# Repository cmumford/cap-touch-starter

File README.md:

# Introduction

This is a simple hardware/software starter project containing an
MCU (ESP32), and a capacitive touch screen. Nothing fancy, just
something to fork when starting a new project that needs these capabilities.

# Main Components

* ESP32-WROVER-E ([Datasheet](https://www.espressif.com/sites/default/files/documentation/esp32-wrover_datasheet_en.pdf))
* [2.8" TFT Display - 240x320 with Capacitive Touchscreen](https://www.adafruit.com/product/2770)
* CP2102N ([Datasheet](https://www.silabs.com/documents/public/data-sheets/cp2102n-datasheet.pdf))
* SPIRAM.
* 10-pin JTAG debug port.

# Board Design

See the [pcb/](pcb/) folder for the schematic and board layout.

# Software

It includes a starter application built with the
[ESP-IDF](https://github.com/espressif/esp-idf) platform framework. The application
[lv_demos](https://github.com/lvgl/lv_demos) which is part of the [LVGL](https://lvgl.io/)
graphics library. This could easily be replaced with a different application

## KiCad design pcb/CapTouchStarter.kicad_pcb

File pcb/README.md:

# Schematic

[Schematic](Schematic.pdf)

# Layout

[Layout](Layout.pdf)

# BOM

| Quantity | Description                      | Value           | Package            |
| -------- | -------------------------------- | --------------- | ------------------ |
| 3        | Capacitor                        | 22μF/6.3V       | 0603 (1608 Metric) |
| 5        | Capacitor                        | 0.1μF/50V       | 0603 (1608 Metric) |
| 1        | Capacitor                        | 4.7μF/6.3V      | 0603 (1608 Metric) |
| 1        | Diode (Schottsky)                | BAT760-7        | SOD-323            |
| 1        | Voltage suppressor               | SP0503BAHT      | SOT-143            |
| 4        | LED                              | LED             | 0603 (1608 Metric) |
| 1        | USB Type-C Receptacle            | [12401548E412A](https://www.digikey.com/en/products/detail/amphenol-icc-commercial-products/12401548E412A/13683580)   |                    |
| 1        | 2.8" LCD w/Capacitive Touch      | [DT280QV10-CT](https://www.adafruit.com/product/2770) |  |
| 1        | Flat pack ribbon cable connector | 62684-502100ALF | 50 pin 0.5 mm pitch |
| 2        | NPN Transistor                   | SS8050-G        | SOT-23             |
| 4        | Resistor                         | 68Ω             | 0603 (1608 Metric) |
| 3        | Resistor                         | 2KΩ             | 0603 (1608 Metric) |
| 1        | Resistor                         | 22K1Ω           | 0603 (1608 Metric) |
| 1        | Resistor                         | 47K5Ω           | 0603 (1608 Metric) |
| 4        | Resistor                         | 10KΩ            | 0603 (1608 Metric) |
| 2        | Resistor                         | 5K1Ω            | 0603 (1608 Metric) |
| 2        | Resistor                         | 2K2Ω            | 0603 (1608 Metric) |
| 1        | ESP32-WROVER-E                   |                 |                    |
| 1        | SPIRAM (8 MB)                    | LY68L6400SLIT   | SOP-8              |
| 1        | Voltage Regulator                | AMS1117-3.3     | SOT-223            |
| 1        | Voltage Detector                 | [BD48K33G-TLCT-ND](https://fscdn.rohm.com/en/products/databook/datasheet/ic/power/voltage_detector/bd48xxg-e.pdf) | SOT-23-3           |
| 1        | USB-to-UART bridge controller    | CP2102N-A01     | QFN-28             |
| 2        | Tactile pushbutton               |                 |                    |
| 1        | Slider 1P2T switch               | SK-12D07        |                    |

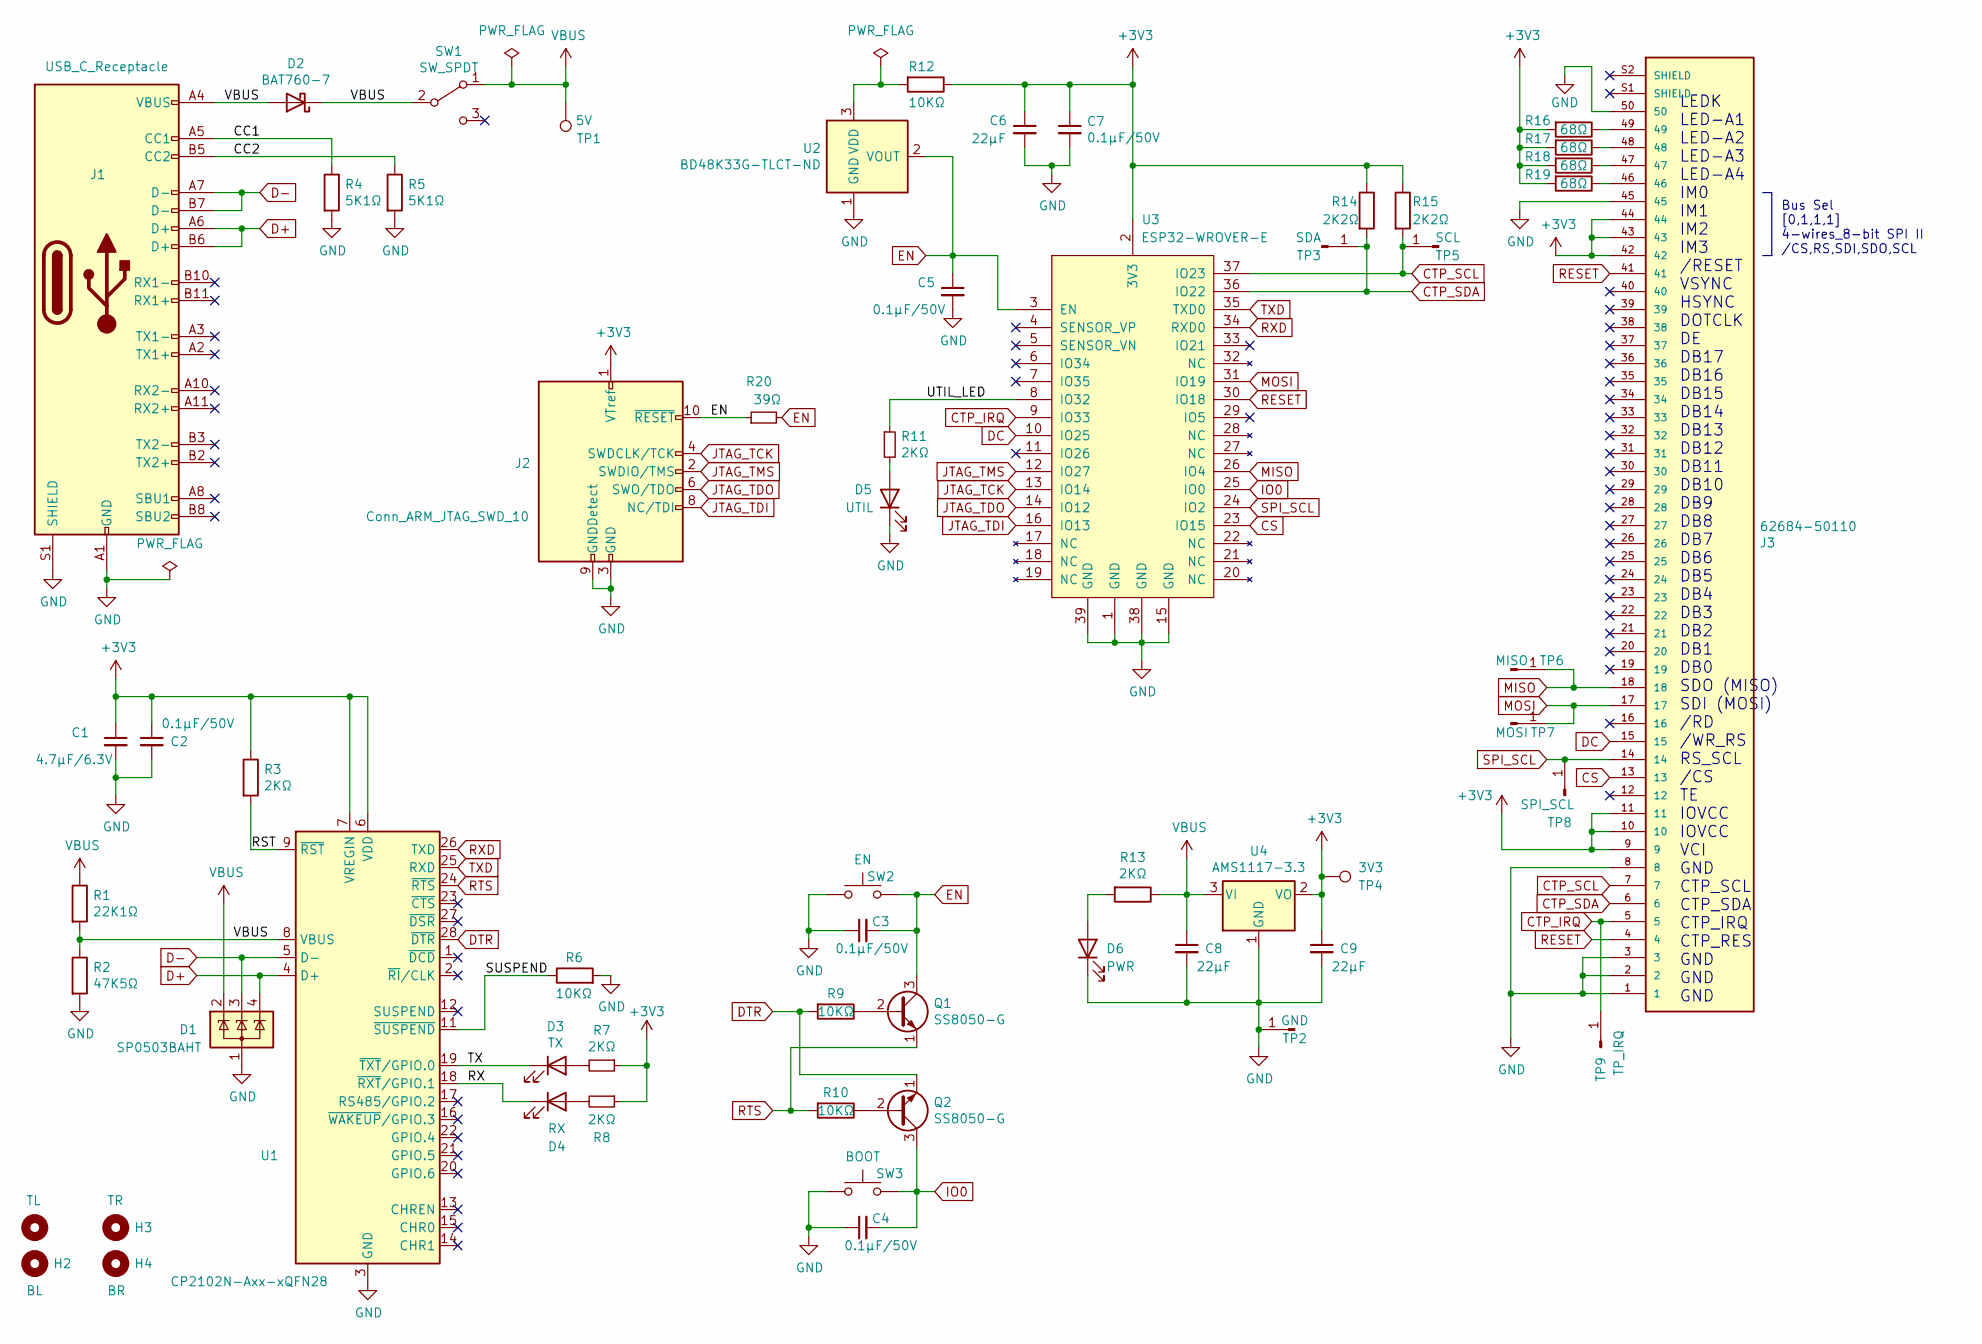
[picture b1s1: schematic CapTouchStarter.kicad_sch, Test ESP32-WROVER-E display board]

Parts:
C1: 4.7μF/6.3V; C_0603_1608Metric
C2, C3, C4, C5, C7: 0.1μF/50V; C_0603_1608Metric
C6, C8, C9: 22μF; C_0603_1608Metric
D1: SP0503BAHT; SOT-143
D2: BAT760-7; D_SOD-323
D3: TX; LED_0603_1608Metric
D4: RX; LED_0603_1608Metric
D5: UTIL; LED_0603_1608Metric
D6: PWR; LED_0603_1608Metric
H1: TL; MountingHole_2.2mm_M2
H2: BL; MountingHole_2.2mm_M2
H3: TR; MountingHole_2.2mm_M2
H4: BR; MountingHole_2.2mm_M2
J1: USB_C_Receptacle; USB_C_Receptacle_Amphenol_12401548E4-2A
J2: Conn_ARM_JTAG_SWD_10; PinHeader_2x05_P1.27mm_Vertical
J3: 62684-50110
Q1, Q2: SS8050-G; SOT-23
R1: 22K1Ω; R_0603_1608Metric
R2: 47K5Ω; R_0603_1608Metric
R3, R7, R8, R11, R13: 2KΩ; R_0603_1608Metric
R4, R5: 5K1Ω; R_0603_1608Metric
R6, R9, R10, R12: 10KΩ; R_0603_1608Metric
R14, R15: 2K2Ω; R_0603_1608Metric
R16, R17, R18, R19: 68Ω; R_0603_1608Metric
R20: 39Ω; R_0603_1608Metric
SW1: SW_SPDT; SW_Slide_1P2T_CK_OS102011MS2Q
SW2: EN; SW_PUSH_6mm_H5mm
SW3: BOOT; SW_PUSH_6mm_H5mm
TP1: 5V; TestPoint_Pad_D2.5mm
TP2: GND; TestPoint_Loop_D2.50mm_Drill1.0mm
TP3: SDA; TestPoint_Loop_D2.50mm_Drill1.0mm
TP4: 3V3; TestPoint_Pad_D2.5mm
TP5: SCL; TestPoint_Loop_D2.50mm_Drill1.0mm
TP6: MISO; TestPoint_Loop_D2.50mm_Drill1.0mm
TP7: MOSI; TestPoint_Loop_D2.50mm_Drill1.0mm
TP8: SPI_SCL; TestPoint_Loop_D2.50mm_Drill1.0mm
TP9: TP_IRQ; TestPoint_Loop_D2.50mm_Drill1.0mm
U1: CP2102N-Axx-xQFN28; QFN-28-1EP_5x5mm_P0.5mm_EP3.35x3.35mm
U2: BD48K33G-TLCT-ND; SOT-23
U3: ESP32-WROVER-E; ESP32-WROVER-IE
U4: AMS1117-3.3; SOT-223-3_TabPin2

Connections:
+3V3: C1.1, C2.1, C6.1, C7.1, C9.1, J2.1 (VTref), J3.9, J3.10, J3.11, J3.42, J3.43, J3.44, R3.1, R7.1, R8.1, R12.1, R14.1, R15.1, R16.2, R17.2, R18.2, R19.2, TP4.1, U1.6 (VDD), U1.7 (VREGIN), U3.2 (3V3), U4.2 (VO)
/CC1: J1.A5 (CC1), R4.1
/CC2: J1.B5 (CC2), R5.1
/RST: R3.2, U1.9 (~RST)
/RX: D4.1 (K), U1.18 (~RXT/GPIO.1)
/SUSPEND: R6.1, U1.11 (~SUSPEND)
/TX: D3.1 (K), U1.19 (~TXT/GPIO.0)
/UTIL_LED: R11.1, U3.8 (IO32)
CS: J3.13, U3.23 (IO15)
CTP_IRQ: J3.5, TP9.1, U3.9 (IO33)
CTP_SCL: J3.7, R15.2, TP5.1, U3.37 (IO23)
CTP_SDA: J3.6, R14.2, TP3.1, U3.36 (IO22)
D+: D1.4 (K), J1.A6 (D+), J1.B6 (D+), U1.4 (D+)
D-: D1.3 (K), J1.A7 (D-), J1.B7 (D-), U1.5 (D-)
DC: J3.15, U3.10 (IO25)
DTR: Q2.1 (E), R9.2, U1.28 (~DTR)
EN: C3.2, C5.1, J2.10 (~RESET), Q1.3 (C), R20.1, R20.2, SW2.2, U2.2 (VOUT), U3.3 (EN)
GND: C1.2, C2.2, C3.1, C4.1, C5.2, C6.2, C7.2, C8.2, C9.2, D1.1 (A), D5.1 (K), D6.1 (K), J1.A1 (GND), J1.A12 (GND), J1.B1 (GND), J1.B12 (GND), J1.S1 (SHIELD), J2.3 (GND), J2.5 (GND), J2.9 (GNDDetect), J3.1, J3.2, J3.3, J3.8, J3.45, J3.50, R2.2, R4.2, R5.2, R6.2, SW2.1, SW3.1, TP2.1, U1.3 (GND), U1.29 (GND), U2.1 (GND), U3.1 (GND), U3.15 (GND), U3.38 (GND), U3.39 (GND), U4.1 (GND)
IO0: C4.2, Q2.3 (C), SW3.2, U3.25 (IO0)
JTAG_TCK: J2.4 (SWDCLK/TCK), U3.13 (IO14)
JTAG_TDI: J2.8 (NC/TDI), U3.16 (IO13)
JTAG_TDO: J2.6 (SWO/TDO), U3.14 (IO12)
JTAG_TMS: J2.2 (SWDIO/TMS), U3.12 (IO27)
MISO: J3.18, TP6.1, U3.26 (IO4)
MOSI: J3.17, TP7.1, U3.31 (IO19)
unnamed: D3.2 (A), R7.2
unnamed: D4.2 (A), R8.2
unnamed: D5.2 (A), R11.2
unnamed: D6.2 (A), R13.2
unnamed: J3.46, R19.1
unnamed: J3.47, R18.1
unnamed: J3.48, R17.1
unnamed: J3.49, R16.1
unnamed: Q1.2 (B), R9.1
unnamed: Q2.2 (B), R10.1
unnamed: R12.2, U2.3 (VDD)
RESET: J3.4, J3.41, U3.30 (IO18)
RTS: Q1.1 (E), R10.2, U1.24 (~RTS)
RXD: U1.26 (TXD), U3.34 (RXD0)
SPI_SCL: J3.14, TP8.1, U3.24 (IO2)
TXD: U1.25 (RXD), U3.35 (TXD0)
VBUS: C8.1, D1.2 (K), D2.1 (K), D2.2 (A), J1.A4 (VBUS), J1.A9 (VBUS), J1.B4 (VBUS), J1.B9 (VBUS), R1.1, R1.2, R2.1, R13.1, SW1.1 (A), SW1.2 (B), TP1.1, U1.8 (VBUS), U4.3 (VI)

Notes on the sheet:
LEDK LED-A1 LED-A2 LED-A3 LED-A4 IM0 IM1 IM2 IM3 /RESET VSYNC HSYNC DOTCLK DE DB17 DB16 DB15 DB14 DB13 DB12 DB11 DB10 DB9 DB8 DB7 DB6 DB5 DB4 DB3 DB2 DB1 DB0 SDO (MISO) SDI (MOSI) /RD /WR_RS RS_SCL /CS TE IOVCC IOVCC VCI GND CTP_SCL CTP_SDA CTP_IRQ CTP_RES GND GND GND
Bus Sel [0,1,1,1] 4-wires_8-bit SPI II /CS,RS,SDI,SDO,SCL

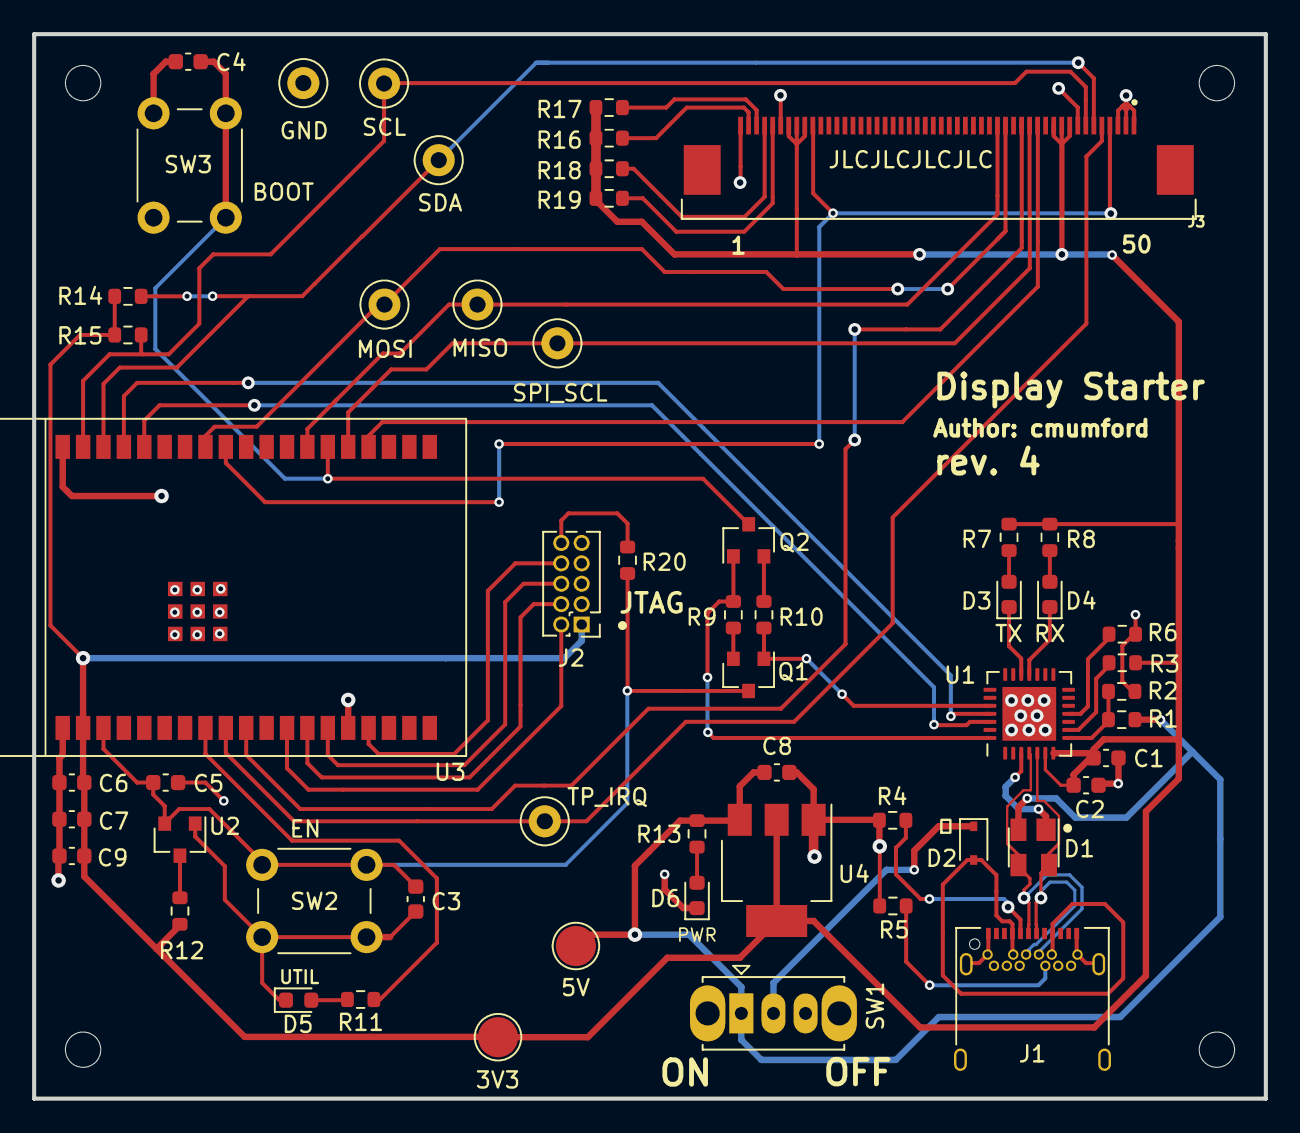
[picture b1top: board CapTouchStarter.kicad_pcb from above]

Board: 4 copper layers, 76.7 x 66.3 mm, 60 parts (0 on the bottom side), 42 nets.

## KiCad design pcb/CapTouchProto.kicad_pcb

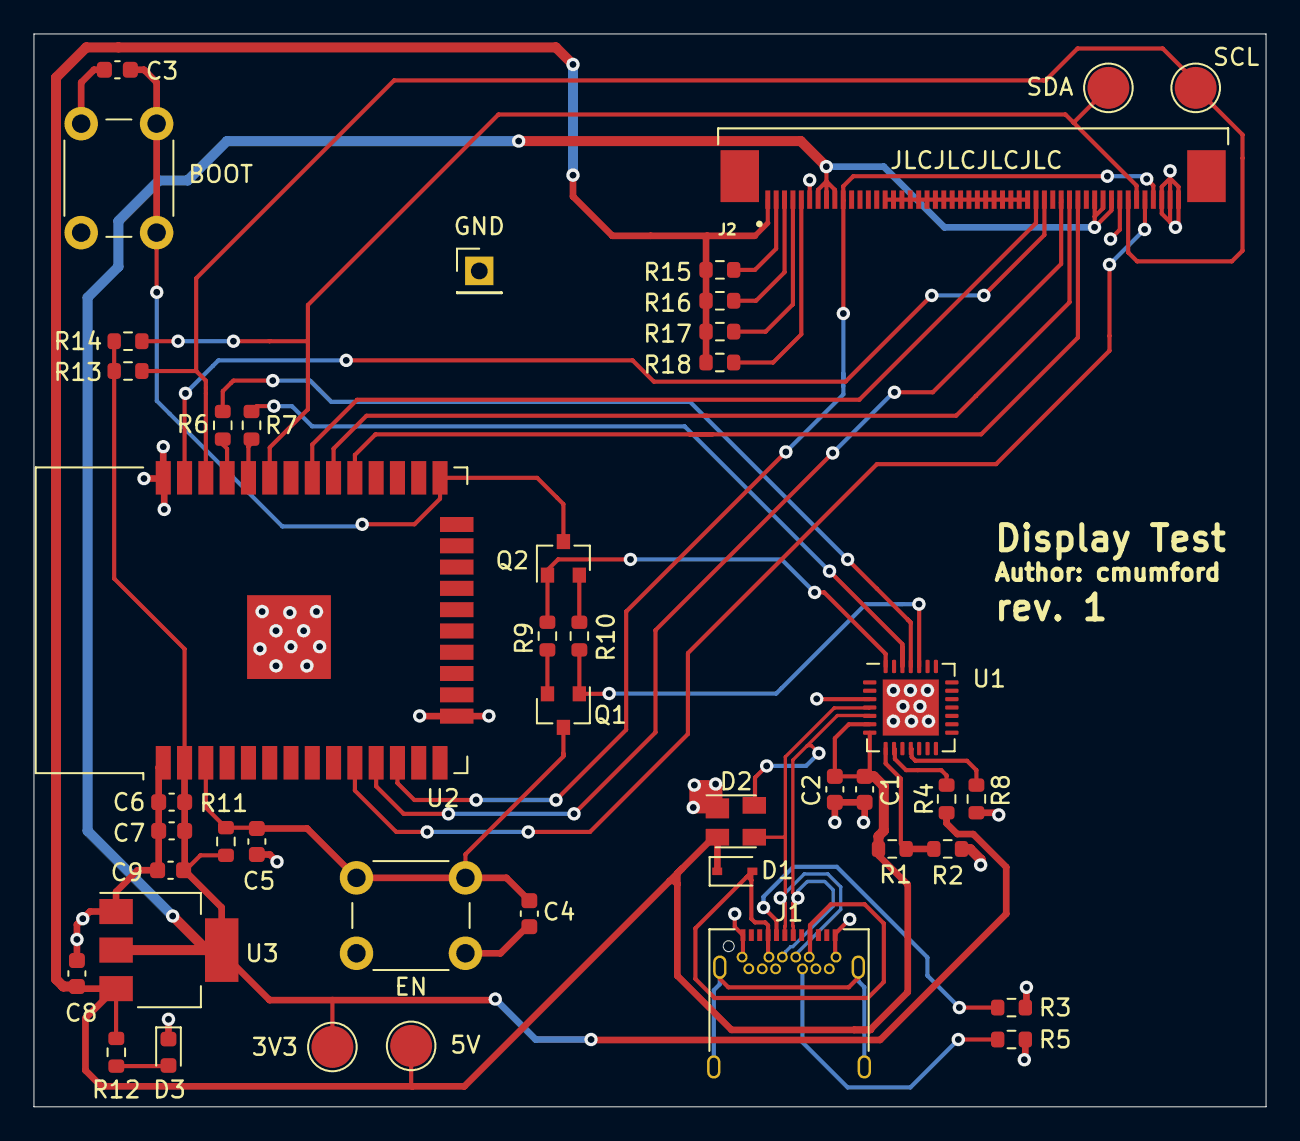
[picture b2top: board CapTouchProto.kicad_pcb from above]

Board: 2 copper layers, 73.5 x 64.0 mm, 44 parts (0 on the bottom side), 36 nets.

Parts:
3V3: 3V3; TestPoint_Pad_D2.5mm
5V: 5V; TestPoint_Pad_D2.5mm
BOOT: SW_Push; SW_PUSH_6mm_H5mm
C1: 4.7μF/6.3V; C_0603_1608Metric
C2: 0.1μF/50V; C_0603_1608Metric
C3, C4, C5, C7: 0.1μF; C_0603_1608Metric
C6, C8, C9: 22μF; C_0603_1608Metric
D1: BAT760-7; D_SOD-323
D2: SP0503BAHT; SOT-143
D3: LED (red); LED_0603_1608Metric
EN: SW_Push; SW_PUSH_6mm_H5mm
GND: Conn_01x01_Male; PinHeader_1x01_P2.54mm_Vertical
J1: USB_C_Receptacle; USB_C_Receptacle_Amphenol_12401548E4-2A
J2: 62684-50110
Q1, Q2: SS8050-G; SOT-23
R1: 22.1KΩ; R_0603_1608Metric
R2: 47.5KΩ; R_0603_1608Metric
R3, R5: 5K1Ω; R_0603_1608Metric
R4: 2KΩ; R_0603_1608Metric
R6, R7: 0Ω; R_0603_1608Metric
R8, R11: 10KΩ; R_0603_1608Metric
R9, R10: 10K; R_0603_1608Metric
R12: 2K (5%); R_0603_1608Metric
R13, R14: 2K2Ω; R_0603_1608Metric
R15, R16, R17, R18: 68Ω; R_0603_1608Metric
SCL: SCL; TestPoint_Pad_D2.5mm
SDA: SDA; TestPoint_Pad_D2.5mm
U1: CP2102N-A01-GQFN28; QFN-28-1EP_5x5mm_P0.5mm_EP3.35x3.35mm
U2: 1965-ESP32-WROOM-32E(8MB)CT-ND; ESP32-WROOM-32
U3: AMS1117-3.3; SOT-223-3_TabPin2

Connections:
+3V3: 3V3.1, C6.1, C7.1, C9.1, J2.7, J2.8, J2.9, J2.40, J2.41, J2.42, R4.1, R11.1, R13.1, R14.1, U2.2, U3.2
D+: D2.3, J1.A6, J1.B6, U1.4
D-: D2.4, J1.A7, J1.B7, U1.5
DTR: Q2.1, R9.2, U1.28
EN: C4.2, C5.1, EN.2, Q1.3, R11.2, U2.3
GND: BOOT.1, C1.2, C2.2, C3.1, C4.1, C5.2, C6.2, C7.2, C8.2, C9.2, D2.1, D3.1, EN.1, GND.1, J1.A1, J1.A12, J1.B1, J1.B12, J2.6, J2.43, J2.48, J2.49, J2.50, R2.2, R3.2, R5.2, R8.2, U1.3, U1.29, U2.1, U2.15, U2.38, U2.39, U3.1
IO0: BOOT.2, C3.2, Q2.3, U2.25
unnamed: D1.2, J1.A4, J1.A9, J1.B4, J1.B9
unnamed: D3.2, R12.2
unnamed: J1.A5, R3.1
unnamed: J1.B5, R5.1
unnamed: J2.2, R15.1
unnamed: J2.3, R16.1
unnamed: J2.4, R17.1
unnamed: J2.5, R18.1
unnamed: J2.10, J2.47, U2.12
unnamed: J2.15, J2.16, J2.17, J2.18, J2.19, J2.20, J2.21, J2.22, J2.23, J2.24, J2.25, J2.26, J2.27, J2.28, J2.29, J2.30, J2.31, J2.32
unnamed: J2.33, U2.31
unnamed: J2.34, U2.37
unnamed: J2.36, U2.11
unnamed: J2.37, U2.30
unnamed: J2.38, U2.29
unnamed: J2.44, R13.2, SCL.1, U2.36
unnamed: J2.45, R14.2, SDA.1, U2.33
unnamed: J2.46, U2.10
unnamed: Q1.2, R9.1
unnamed: Q2.2, R10.1
unnamed: R1.2, R2.1, U1.8
unnamed: R4.2, U1.9
unnamed: R6.2, U1.25
unnamed: R7.2, U1.26
unnamed: R8.1, U1.11
RTS: Q1.1, R10.2, U1.24
RXD: R7.1, U2.34
TXD: R6.1, U2.35
VBUS: 5V.1, C1.1, C2.1, C8.1, D1.1, D2.2, J2.1, R1.1, R12.1, R15.2, R16.2, R17.2, R18.2, U1.6, U1.7, U3.3

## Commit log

2021-09-04 Added .gitattributes.
2021-09-04 Added .gitignore.
2021-09-04 Add footprint+symbol for 62684-50110.
    This is a 50-pin 0.5mm pitch flat panel connector (FPC).
    https://www.adafruit.com/product/1492
2021-09-04 Added flat panel connector to schematic.
2021-09-05 Some schematic wire-up.
2021-09-05 Add ESP32-WROOM-32E symbol+footprint.
2021-09-05 Lots of connecting up stuff.
2021-09-05 A little layout.
2021-09-06 more layout.
2021-09-06 Layout of usb-c power.
2021-09-06 Getting closer.
2021-09-06 Transistors to SOT-23.
2021-09-06 power routed.
2021-09-06 USB-C 5.1K resistor layout.
2021-09-06 Layout done.
2021-09-06 Specified 6mmx5mm tactile buttons.
2021-09-06 Add test points.
2021-09-07 Settings for creating Gerber files.
2021-09-07 Add schematic + board layout PDFs.
2021-09-25 Added dot for CP2102N pin 1.
2021-09-26 Moved some passives on layout for better labeling.
2021-09-26 Testpoint changes.
2021-09-26 Fix switch labeling, more cleanup.
2021-09-26 CP2102 VCC/REGIN pins to 3.3V instead of VBUS.
    Oops!
2021-10-02 STL for 5-1734592-0
    From https://www.te.com/usa-en/product-5-1734592-0.html
2021-10-03 Added README.
2021-10-03 Unified value names.
    Renamed component values so that the coalesce into groups
    when creating a BOM.
2021-10-03 Added submodules: lvgl, lvgl_esp32_drivers.
2021-10-08 Added project build files.
2021-10-08 Set pins for this board.
    Working for ESP32-WROOM-32D.
    I believe this has no integrated SPIRAM.
2021-10-08 Added README docs.
2021-10-08 Add lv_examples.
    Add the lv_examples submodule and use the widget slideshow
    as the application main body.
2021-10-08 Printing out memory info at startup.
    ```
    I (317) App: CapTouchProto app!
    I (317) App: This is esp32 chip with 2 CPU core(s), WiFi/BT/BLE.
    I (327) App: Silicon revision 3.
    I (327) App: 4 MB external flash
    I (337) App: Free heap size: 292772 bytes.
2021-10-08 Upgraded LVGL to v8.
2021-10-08 Increased external SPI flash size to 4MB.
2021-10-08 Git-ignoring build/ & sdkconfig.
2021-10-08 Added application boilerplate.
2021-10-08 sdkconfig: Defining LVGL fonts.
2021-10-10 Switched display mode to 4-wires_8-bit SPI.
    Set the interface mode pins (IM0..IM3) to [0, 1, 1, 0].
2021-10-10 Connected display backlight cathode (LEDK) to GND.
2021-10-10 WIP: Changes to LVGL Display config.
2021-10-10 Renamed KiCad project files to match repo name.
2021-10-10 Using 3V3 for display VCC.
2021-10-10 sdkconfig: Added section comments.
    Makes comparing configured defaults easier.
2021-10-10 Added script to delete files.
    Simplify the cleaning process with a script to delete files/dirs.
    Adding this because PowerShell's Remove-Item command doesn't take
    multiple args, and also returns a non-zero error code for nonexistent
    items - even with the `-ErrorAction Ignore` argument.
2021-10-10 LVGL display: VSPI, MISO.
2021-10-10 Disabled custom LVGL SPI frequency.
2021-10-10 LVGL: half => full duplex.
2021-10-10 display sdkconfig.default values.
2021-10-11 sdkconfig: Added FT6X06 touch controller to LVGL config.
    Board uses FT6206 touch controller. Using I2C bus 0 with standard
    configuration.
2021-10-11 Back to 4-wire SPI II bus.
    Bus Sel
    [0,1,1,1]
    4-wires_8-bit SPI II
    /CS,RS,SDI,SDO,SCL
2021-10-11 Corrected LCD pin order.
    The 50-pin flat pack ribbon cable has reversed pin ordering.
2021-10-11 Removed 0Ω TX/RX resistors.
    Also minor routing cleanup.
2021-10-11 Added TX/RX LED's.
    Also, layout cleanup.
2021-10-11 Update layout/schematic PDFs.
    And update board design version to 2.
2021-10-11 Added display silkscreen pin numbers.
2021-10-11 Add SPI test points.
2021-10-12 Use global labels to cleanup schematic.
2021-10-12 Move GND test pad below voltage regulator in schematic.
    No changes to layout.
2021-10-12 Combine DTR/RTS EN/IO0 sections.
2021-10-12 Add JTAG debugger connector.
2021-10-12 Add pin 1 identifiers.
    Also move 3V3 and 5V test pads (make inline).
2021-10-12 Import JLCPCB design rules for 1-2 layer boards.
    Source: https://github.com/sethhillbrand/kicad_templates
2021-10-12 Updated PDFs.
2021-11-13 Using FPC STP file.
2021-11-13 Add a voltage detector.
    Add a BD48K33G-TLCT-ND voltage detector.
2021-11-13 Added power switch.
    A horizontal slider switch to enable/disable entire device.
2021-11-13 More route cleanup.
2021-11-13 Documented starter source.
2021-11-13 Disabled built-in ESP32 I2C pullup resistors.
2021-11-13 pcb: Very minor alignments and clenup.
2021-11-13 pcb: Added r3. TODO items.
2021-11-13 Added library for LY68L6400SLIT.
    https://datasheet.lcsc.com/lcsc/1809140531_Lyontek-Inc--LY68L6400SLIT_C261881.pdf
2021-11-13 Moved TP_IRQ label.
2021-11-13 Disabled mbedTLS trusted root certificate bundle.
    Certificate bundle has expired/invalid certs, so disabled as per:
    See https://github.com/espressif/esp-idf/issues/7621
    This should be temporary once ESP-IDF is updated.
2021-11-13 Resetting touch panel.
2021-11-13 Layout with PSRAM.
2021-11-13 Added 50-pin FPC connector symbol.
    Molex.
    Mfr. part: 0541325062
2021-11-13 Updated schematic PDF.
2021-11-13 Using pdMS_TO_TICKS macro.
2021-11-13 Cleanup.
2021-11-13 Added mounting holes for standoffs.
    Not pretty, but should work.
2021-11-13 Added PSRAM to circuit.
    https://pcbartists.com/design/embedded/esp32-psram-schematic-notes/
2021-11-13 Rename lv_examples to lv_demos.
    lv_examples seems to have been renamed upstream to lv_demos. Navigating
    to https://github.com/lvgl/lv_examples.git redirects to
    https://github.com/lvgl/lv_demos. This projects lv_examples directory
    started out as a copy of
    https://github.com/lvgl/lv_port_esp32/tree/master/components/lv_examples
    which appears to be before the rename.
2021-11-13 Moved voltage regulator in layout.
2021-11-13 Ordered pcb todo by priority.
2021-11-13 Added antenna keep-out zone for copper fill.
2021-11-13 Fixed ground via overlapping display anchor pad.
2021-11-13 Removed 0Ω resistors from the BOM.
    These were in rev 1 for testing, but no longer used.
2021-11-13 Fix LCD product link.
2021-11-13 Improve software description in README.
2021-11-13 Move pushbutton near switch in README
    Like with like.
2021-11-13 Added serial port enumerators.
2021-11-13 Add openocd target.
2021-11-14 Added utility LED connected to IO32.
2021-11-14 Added voltage detector datasheet link.
2021-11-14 Got LED's working.
    No change required. Needed to use Simplicity Studio's Xpress
    Configurator to set GPIO0/1's alternate configuration to
    TX/RX Toggle respectively.
2021-11-14 Figured out capacitive touch issue.
    Corrent board has a solder bridge that shorts SCL to GND. Hopefully
    that is the only problem.
2021-11-14 Keepig current ESD solution.
    May change in a future rev.
2021-11-14 Refilled ground pour.
2021-11-14 Updated layout/schematic PDFs.
2021-11-14 Add missing trace for UTIL LED.
2021-11-14 New layout PDF.
2021-11-14 Added board render image.
2021-11-14 Added SPIRAM to README.
2021-11-15 README text tweak.
2021-11-26 Changed schematic version to 3.
2021-11-26 Cleaning KiCAD intermediate files.
2021-11-26 Add more space between GND and 3v3 on display connector.
2021-11-26 Switched JTAG footprint to 3220-10-0100-00.
2021-11-26 Turning on UTIL LED at boot.
2021-11-26 Add library symbol/footprint for 3220-10-0100-00.
    a 2x5 1.27 mm connector for JTAG debugger port.
    https://www.digikey.com/en/products/detail/cnc-tech/3220-10-0100-00/3883661
2021-11-26 Added SS-52400-003 USB Type-C connector footprint/symbol.
    Added to library.
    https://www.digikey.com/en/products/detail/stewart-connector/SS-52400-003/11205655
2021-11-26 pcb: swapped on/off label positions.
2021-11-26 Added USB C connector 3d model.
    Not the correct model - just a placeholder.
2021-11-26 Added SPIRAM to BOM.
    Using LY68L6400SLIT.
2021-11-26 Added Makefile ${CHIP} variable.
2021-11-26 pcb: Added USB connector link.
2021-11-26 pcb: Changed revision to 4.
2021-11-26 pcb: Added layout metadata.
2021-11-27 Added 3220-10-0100-00 datasheet.
2021-11-27 Added debug LED blink task.
2021-11-27 Added SPI RAM sections on sdkconfig.defaults.
    No values - just the comments to delineate sections.
2021-11-28 Set display part no.
2021-11-28 Updated MCU/SPIRAM in README.
2021-11-29 Add ESP32-WROVER-E KiCAD symbol/footprint library.
    Source: https://github.com/cmumford/ESP32-WROVER-E.git
    which is a fork of https://github.com/kaevee/ESP32-WROVER-E.
2021-12-02 Change layout for ESP32-WROVER-E.
2021-12-02 Reverted JTAG back to PinHeader_2x05_P1.27mm_Vertical
    The 3220-10-0100-00 footprint didn't pass the DRT checks
    for JLCPCB's manufacturering specifications.
    This is a revert of e6e3ab1.
2021-12-02 Switched to ESP32-WROVER-E footprint w/courtyard.
2021-12-02 Added NC to unused ESP32 pins.
2021-12-02 Changed chip type to ESP32-WROVER-E.
2021-12-02 Change app pins to match changed board.
2021-12-04 hid off-board "keep out area" silkscreen.
2022-01-23 Upgraded to KiCAD 6.
2022-01-23 Deleted unconnected tracks.
    And one unnecessary via.
2022-01-23 More DRC fixes.
2022-01-23 Switched to KiCAD 6 CP2102N symbol.
    It looks like the v5 CP2102N-A01-GQFN28 symbol was renamed
    to CP2102N-Axx-xQFN28 in v6.
2022-01-23 Cleanup and IO0 route fix.
2022-01-24 Added PWR_FLAG to help pass ERC.
2022-01-25 Add JTAG RESET series resistor.
    Eliminate the following ERC warning:
    "Pins of type Output and Open collector are connector".
    Discussion at
    https://www.reddit.com/r/AskElectronics/comments/754epz/series_resistors_on_jtag_lines/
    Also, fixed D+/D- ESD pad assignments and a few silkscreen inside
    cut boundaries ERC warnings.
2022-01-26 Deleleted KiCAD local settings file.
2022-01-30 Switch to cmumford-components for KiCad components.
    https://github.com/cmumford/cmumford-components.git
2022-01-30 Specifying USB-C STP file.
    The built-in Connector_USB:USB_C_Receptacle_Amphenol_12401548E4-2A
    footprint's STP file produces this error:
    File not found
    ${KICAD6_3DMODEL_DIR}/Connector_USB.3dshapes/USB_C_Receptacle_Amphenol_12401548E4-2A.wrl
    Using the STP file from
    https://www.amphenol-icc.com/usb3-2-gen2-12401548e412a.html
2022-01-31 Updated footprint for "50-pin 0.5mm pitch top-contact FPC SMT Connector"
2022-02-04 Using ESP32-WROVER-E 3D model.
2022-03-11 Added network labels.
2022-03-13 Using ${REVISION} variable.
2022-03-17 Made default build target build.
